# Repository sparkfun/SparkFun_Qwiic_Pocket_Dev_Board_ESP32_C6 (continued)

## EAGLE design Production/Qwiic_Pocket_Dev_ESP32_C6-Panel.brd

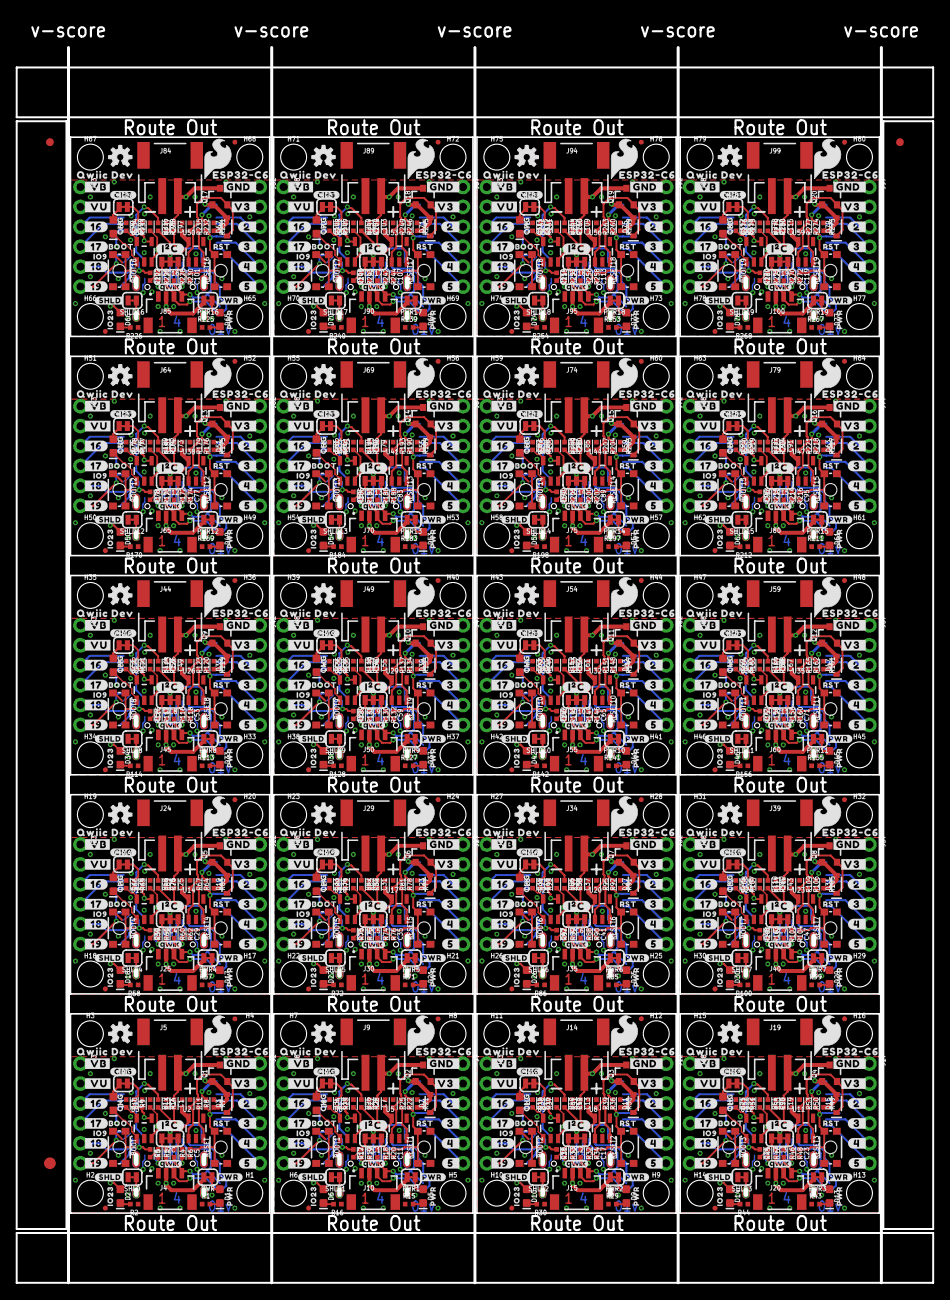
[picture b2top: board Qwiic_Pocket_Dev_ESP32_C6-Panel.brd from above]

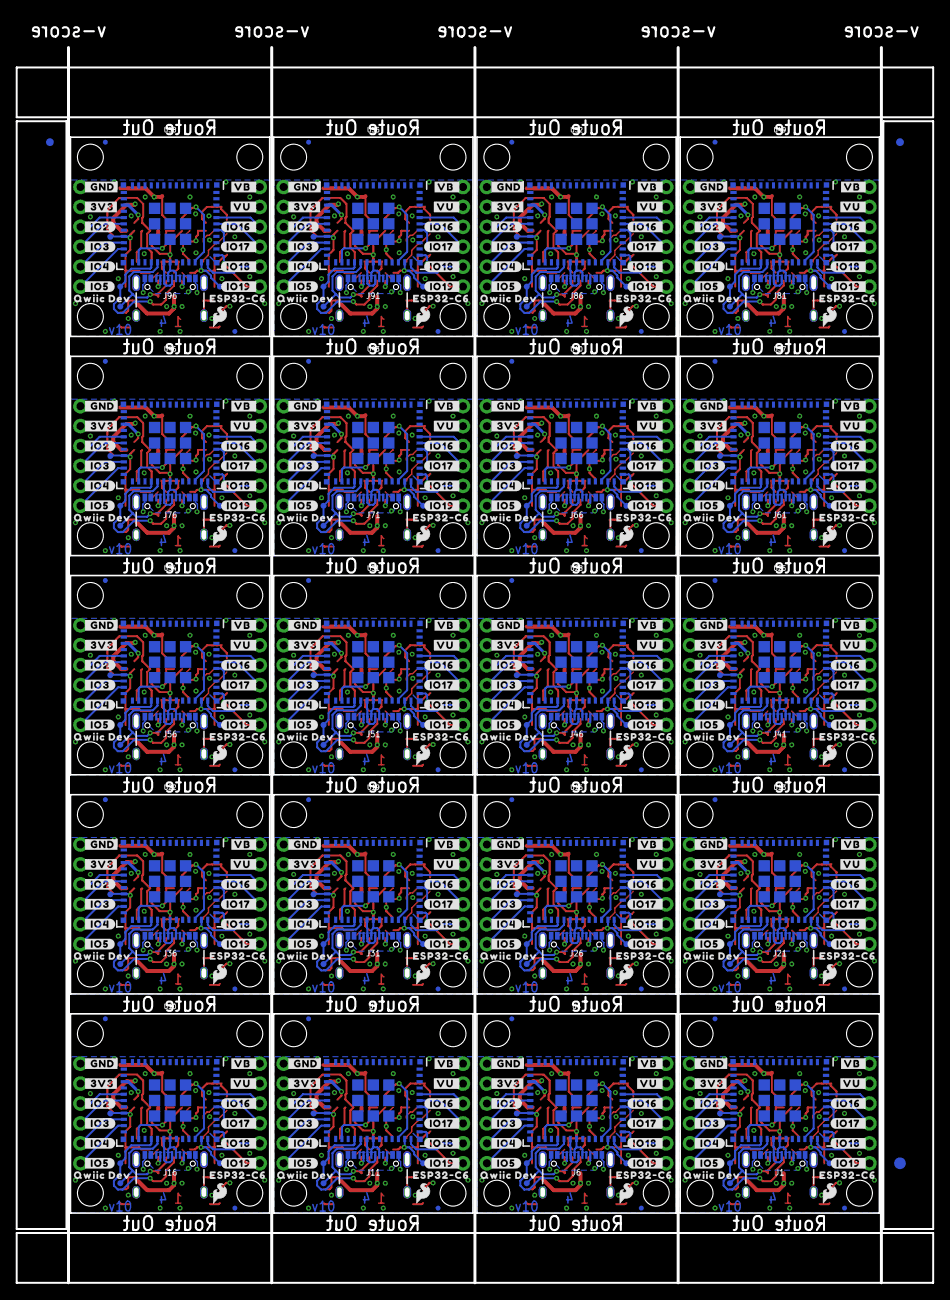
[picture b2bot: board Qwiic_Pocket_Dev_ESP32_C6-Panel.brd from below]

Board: 4 copper layers, 116.8 x 157.5 mm, 1906 parts (463 on the bottom side), 700 nets.

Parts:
BOOT, BOOT1, BOOT2, BOOT3, BOOT4, BOOT5, BOOT6, BOOT7, BOOT8, BOOT9, BOOT10, BOOT11, BOOT12, BOOT13, BOOT14, BOOT15, BOOT16, BOOT17, BOOT18, BOOT19: MOMENTARY-SWITCH-SPST-SMD-4.6X2.8MM; TACTILE_SWITCH_SMD_4.6X2.8MM
C1, C2, C3, C4, C7, C8, C9, C10, C13, C14, C15, C16, C19, C20, C21, C22, C25, C26, C27, C28, C31, C32, C33, C34, C37, C38, C39, C40, C43, C44, C45, C46, C49, C50, C51, C52, C55, C56, C57, C58, C61, C62, C63, C64, C67, C68, C69, C70, C73, C74, C75, C76, C79, C80, C81, C82, C85, C86, C87, C88, C91, C92, C93, C94, C97, C98, C99, C100, C103, C104, C105, C106, C109, C110, C111, C112, C115, C116, C117, C118: 2.2uF; 0402-TIGHT
C5, C11, C17, C23, C29, C35, C41, C47, C53, C59, C65, C71, C77, C83, C89, C95, C101, C107, C113, C119: 0.1uF; 0402-TIGHT
C6, C12, C18, C24, C30, C36, C42, C48, C54, C60, C66, C72, C78, C84, C90, C96, C102, C108, C114, C120: DNP; 0402-TIGHT
CHG, CHG1, CHG2, CHG3, CHG4, CHG5, CHG6, CHG7, CHG8, CHG9, CHG10, CHG11, CHG12, CHG13, CHG14, CHG15, CHG16, CHG17, CHG18, CHG19: JUMPER-SMT_2_NC_TRACE_SILK; SMT-JUMPER_2_NC_TRACE_SILK
D1, D5, D9, D13, D17, D21, D25, D29, D33, D37, D41, D45, D49, D53, D57, D61, D65, D69, D73, D77: LED-0603
D2, D6, D10, D14, D18, D22, D26, D30, D34, D38, D42, D46, D50, D54, D58, D62, D66, D70, D74, D78: BLUE; LED-0603
D3, D7, D11, D15, D19, D23, D27, D31, D35, D39, D43, D47, D51, D55, D59, D63, D67, D71, D75, D79: 1A/23V/620mV; SOD-323
D4, D8, D12, D16, D20, D24, D28, D32, D36, D40, D44, D48, D52, D56, D60, D64, D68, D72, D76, D80: Yellow; LED-0603
E$1, E$2, E$3, E$4: FIDUCIAL-1X2
E$5, E$6: FIDUCIAL-1.5X3
FD1, FD2, FD3, FD4, FD5, FD6, FD7, FD8, FD9, FD10, FD11, FD12, FD13, FD14, FD15, FD16, FD17, FD18, FD19, FD20, FD21, FD22, FD23, FD24, FD25, FD26, FD27, FD28, FD29, FD30, FD31, FD32, FD33, FD34, FD35, FD36, FD37, FD38, FD39, FD40, FD41, FD42, FD43, FD44, FD45, FD46, FD47, FD48, FD49, FD50, FD51, FD52, FD53, FD54, FD55, FD56, FD57, FD58, FD59, FD60, FD61, FD62, FD63, FD64, FD65, FD66, FD67, FD68, FD69, FD70, FD71, FD72, FD73, FD74, FD75, FD76, FD77, FD78, FD79, FD80: FIDUCIALUFIDUCIAL; FIDUCIAL-MICRO
FRAME1, FRAME2, FRAME3, FRAME4, FRAME5, FRAME6, FRAME7, FRAME8, FRAME9, FRAME10, FRAME11, FRAME12, FRAME13, FRAME14, FRAME15, FRAME16, FRAME17, FRAME18, FRAME19, FRAME20: FRAME-LETTER; CREATIVE_COMMONS
H1, H2, H3, H4, H5, H6, H7, H8, H9, H10, H11, H12, H13, H14, H15, H16, H17, H18, H19, H20, H21, H22, H23, H24, H25, H26, H27, H28, H29, H30, H31, H32, H33, H34, H35, H36, H37, H38, H39, H40, H41, H42, H43, H44, H45, H46, H47, H48, H49, H50, H51, H52, H53, H54, H55, H56, H57, H58, H59, H60, H61, H62, H63, H64, H65, H66, H67, H68, H69, H70, H71, H72, H73, H74, H75, H76, H77, H78, H79, H80: STAND-OFF
I2C, I2C1, I2C2, I2C3, I2C4, I2C5, I2C6, I2C7, I2C8, I2C9, I2C10, I2C11, I2C12, I2C13, I2C14, I2C15, I2C16, I2C17, I2C18, I2C19: JUMPER-SMT_3_2-NC_TRACE_SILK; SMT-JUMPER_3_2-NC_TRACE_SILK
J1, J6, J11, J16, J21, J26, J31, J36, J41, J46, J51, J56, J61, J66, J71, J76, J81, J86, J91, J96: USB Female Type C Connector; USB-C-16P_4LAYER-PADS
J2, J3, J7, J8, J12, J13, J17, J18, J22, J23, J27, J28, J32, J33, J37, J38, J42, J43, J47, J48, J52, J53, J57, J58, J62, J63, J67, J68, J72, J73, J77, J78, J82, J83, J87, J88, J92, J93, J97, J98: 1X06_NO_SILK
J4, J10, J15, J20, J25, J30, J35, J40, J45, J50, J55, J60, J65, J70, J75, J80, J85, J90, J95, J100: QWIIC_RIGHT_ANGLE; JST04_1MM_RA
J5, J9, J14, J19, J24, J29, J34, J39, J44, J49, J54, J59, J64, J69, J74, J79, J84, J89, J94, J99: JST-2-SMD
LOGO1, LOGO4, LOGO7, LOGO10, LOGO13, LOGO16, LOGO19, LOGO22, LOGO25, LOGO28, LOGO31, LOGO34, LOGO37, LOGO40, LOGO43, LOGO46, LOGO49, LOGO52, LOGO55, LOGO58: SFE_LOGO_NAME_FLAMEBLANK; BLANK
LOGO2, LOGO5, LOGO8, LOGO11, LOGO14, LOGO17, LOGO20, LOGO23, LOGO26, LOGO29, LOGO32, LOGO35, LOGO38, LOGO41, LOGO44, LOGO47, LOGO50, LOGO53, LOGO56, LOGO59: OSHW-LOGOS; OSHW-LOGO-S
LOGO3, LOGO6, LOGO9, LOGO12, LOGO15, LOGO18, LOGO21, LOGO24, LOGO27, LOGO30, LOGO33, LOGO36, LOGO39, LOGO42, LOGO45, LOGO48, LOGO51, LOGO54, LOGO57, LOGO60: QWIIC_LOGO_3MM; QWIIC_3MM
PWR, PWR1, PWR2, PWR3, PWR4, PWR5, PWR6, PWR7, PWR8, PWR9, PWR10, PWR11, PWR12, PWR13, PWR14, PWR15, PWR16, PWR17, PWR18, PWR19: JUMPER-SMT_2_NC_TRACE_SILK; SMT-JUMPER_2_NC_TRACE_SILK
Q1, Q2, Q3, Q4, Q5, Q6, Q7, Q8, Q9, Q10, Q11, Q12, Q13, Q14, Q15, Q16, Q17, Q18, Q19, Q20: 20V/4.2A/52mΩ/1.4W; SOT23-3
R1, R9, R10, R15, R23, R24, R29, R37, R38, R43, R51, R52, R57, R65, R66, R71, R79, R80, R85, R93, R94, R99, R107, R108, R113, R121, R122, R127, R135, R136, R141, R149, R150, R155, R163, R164, R169, R177, R178, R183, R191, R192, R197, R205, R206, R211, R219, R220, R225, R233, R234, R239, R247, R248, R253, R261, R262, R267, R275, R276: 4.7k; 0402-TIGHT
R2, R3, R4, R16, R17, R18, R30, R31, R32, R44, R45, R46, R58, R59, R60, R72, R73, R74, R86, R87, R88, R100, R101, R102, R114, R115, R116, R128, R129, R130, R142, R143, R144, R156, R157, R158, R170, R171, R172, R184, R185, R186, R198, R199, R200, R212, R213, R214, R226, R227, R228, R240, R241, R242, R254, R255, R256, R268, R269, R270: 2.2k; 0402-TIGHT
R5, R6, R19, R20, R33, R34, R47, R48, R61, R62, R75, R76, R89, R90, R103, R104, R117, R118, R131, R132, R145, R146, R159, R160, R173, R174, R187, R188, R201, R202, R215, R216, R229, R230, R243, R244, R257, R258, R271, R272: 5.1k; 0402-TIGHT
R7, R8, R11, R12, R21, R22, R25, R26, R35, R36, R39, R40, R49, R50, R53, R54, R63, R64, R67, R68, R77, R78, R81, R82, R91, R92, R95, R96, R105, R106, R109, R110, R119, R120, R123, R124, R133, R134, R137, R138, R147, R148, R151, R152, R161, R162, R165, R166, R175, R176, R179, R180, R189, R190, R193, R194, R203, R204, R207, R208, R217, R218, R221, R222, R231, R232, R235, R236, R245, R246, R249, R250, R259, R260, R263, R264, R273, R274, R277, R278: 100k; 0402-TIGHT
R13, R14, R27, R28, R41, R42, R55, R56, R69, R70, R83, R84, R97, R98, R111, R112, R125, R126, R139, R140, R153, R154, R167, R168, R181, R182, R195, R196, R209, R210, R223, R224, R237, R238, R251, R252, R265, R266, R279, R280: 1M; 0402-TIGHT
RESET, RESET1, RESET2, RESET3, RESET4, RESET5, RESET6, RESET7, RESET8, RESET9, RESET10, RESET11, RESET12, RESET13, RESET14, RESET15, RESET16, RESET17, RESET18, RESET19: MOMENTARY-SWITCH-SPST-SMD-4.6X2.8MM; TACTILE_SWITCH_SMD_4.6X2.8MM
SHLD, SHLD1, SHLD2, SHLD3, SHLD4, SHLD5, SHLD6, SHLD7, SHLD8, SHLD9, SHLD10, SHLD11, SHLD12, SHLD13, SHLD14, SHLD15, SHLD16, SHLD17, SHLD18, SHLD19: JUMPER-SMT_2_NC_TRACE_SILK; SMT-JUMPER_2_NC_TRACE_SILK
TP1, TP2, TP3, TP4, TP5, TP6, TP7, TP8, TP9, TP10, TP11, TP12, TP13, TP14, TP15, TP16, TP17, TP18, TP19, TP20, TP21, TP22, TP23, TP24, TP25, TP26, TP27, TP28, TP29, TP30, TP31, TP32, TP33, TP34, TP35, TP36, TP37, TP38, TP39, TP40, TP41, TP42, TP43, TP44, TP45, TP46, TP47, TP48, TP49, TP50, TP51, TP52, TP53, TP54, TP55, TP56, TP57, TP58, TP59, TP60, TP61, TP62, TP63, TP64, TP65, TP66, TP67, TP68, TP69, TP70, TP71, TP72, TP73, TP74, TP75, TP76, TP77, TP78, TP79, TP80: TEST-POINT3; PAD.03X.03
U1, U4, U7, U10, U13, U16, U19, U22, U25, U28, U31, U34, U37, U40, U43, U46, U49, U52, U55, U58: ESP32-C6-MINI-1
U2, U5, U8, U11, U14, U17, U20, U23, U26, U29, U32, U35, U38, U41, U44, U47, U50, U53, U56, U59: RT9080-33GJ5; SOT23-5
U3, U6, U9, U12, U15, U18, U21, U24, U27, U30, U33, U36, U39, U42, U45, U48, U51, U54, U57, U60: MCP73831; SOT23-5
U$1, U$4, U$81, U$121, U$161, U$201, U$241, U$281, U$321, U$361, U$401, U$441, U$481, U$521, U$561, U$601, U$641, U$681, U$721, U$761: #_GND#0
U$2, U$24, U$82, U$122, U$162, U$202, U$242, U$282, U$322, U$362, U$402, U$442, U$482, U$522, U$562, U$602, U$642, U$682, U$722, U$762: #_3V3#0
U$3, U$72, U$112, U$152, U$192, U$232, U$272, U$312, U$352, U$392, U$432, U$472, U$512, U$552, U$592, U$632, U$672, U$712, U$752, U$792: #V3_#0
U$5, U$71, U$111, U$151, U$191, U$231, U$271, U$311, U$351, U$391, U$431, U$471, U$511, U$551, U$591, U$631, U$671, U$711, U$751, U$791: #GND_#0
U$6, U$73, U$113, U$153, U$193, U$233, U$273, U$313, U$353, U$393, U$433, U$473, U$513, U$553, U$593, U$633, U$673, U$713, U$753, U$793: SFE_LOGO_FLAME_.2
U$7, U$53, U$93, U$133, U$173, U$213, U$253, U$293, U$333, U$373, U$413, U$453, U$493, U$533, U$573, U$613, U$653, U$693, U$733, U$773: #VU_#0
U$8, U$54, U$94, U$134, U$174, U$214, U$254, U$294, U$334, U$374, U$414, U$454, U$494, U$534, U$574, U$614, U$654, U$694, U$734, U$774: #_VB#0
U$9, U$25, U$78, U$79, U$118, U$119, U$158, U$159, U$198, U$199, U$238, U$239, U$278, U$279, U$318, U$319, U$358, U$359, U$398, U$399, U$438, U$439, U$478, U$479, U$518, U$519, U$558, U$559, U$598, U$599, U$638, U$639, U$678, U$679, U$718, U$719, U$758, U$759, U$798, U$799: QWIIC_DEV0
U$10, U$74, U$114, U$154, U$194, U$234, U$274, U$314, U$354, U$394, U$434, U$474, U$514, U$554, U$594, U$634, U$674, U$714, U$754, U$794: SFE_LOGO_FLAME_.1
U$11, U$12, U$75, U$76, U$115, U$116, U$155, U$156, U$195, U$196, U$235, U$236, U$275, U$276, U$315, U$316, U$355, U$356, U$395, U$396, U$435, U$436, U$475, U$476, U$515, U$516, U$555, U$556, U$595, U$596, U$635, U$636, U$675, U$676, U$715, U$716, U$755, U$756, U$795, U$796: ESP32#C633
U$13, U$55, U$95, U$135, U$175, U$215, U$255, U$295, U$335, U$375, U$415, U$455, U$495, U$535, U$575, U$615, U$655, U$695, U$735, U$775: #_IO5#0
U$14, U$56, U$96, U$136, U$176, U$216, U$256, U$296, U$336, U$376, U$416, U$456, U$496, U$536, U$576, U$616, U$656, U$696, U$736, U$776: #_IO4#0
U$15, U$57, U$97, U$137, U$177, U$217, U$257, U$297, U$337, U$377, U$417, U$457, U$497, U$537, U$577, U$617, U$657, U$697, U$737, U$777: #_IO3#0
U$16, U$58, U$98, U$138, U$178, U$218, U$258, U$298, U$338, U$378, U$418, U$458, U$498, U$538, U$578, U$618, U$658, U$698, U$738, U$778: #_IO2#0
U$17, U$59, U$99, U$139, U$179, U$219, U$259, U$299, U$339, U$379, U$419, U$459, U$499, U$539, U$579, U$619, U$659, U$699, U$739, U$779: #IO16_#0
U$18, U$60, U$100, U$140, U$180, U$220, U$260, U$300, U$340, U$380, U$420, U$460, U$500, U$540, U$580, U$620, U$660, U$700, U$740, U$780: #IO17_#0
U$19, U$61, U$101, U$141, U$181, U$221, U$261, U$301, U$341, U$381, U$421, U$461, U$501, U$541, U$581, U$621, U$661, U$701, U$741, U$781: #IO18_#0
U$20, U$62, U$102, U$142, U$182, U$222, U$262, U$302, U$342, U$382, U$422, U$462, U$502, U$542, U$582, U$622, U$662, U$702, U$742, U$782: #IO19_#0
U$21, U$63, U$103, U$143, U$183, U$223, U$263, U$303, U$343, U$383, U$423, U$463, U$503, U$543, U$583, U$623, U$663, U$703, U$743, U$783: #5_#0
U$22, U$64, U$104, U$144, U$184, U$224, U$264, U$304, U$344, U$384, U$424, U$464, U$504, U$544, U$584, U$624, U$664, U$704, U$744, U$784: #4_#0
U$23, U$77, U$117, U$157, U$197, U$237, U$277, U$317, U$357, U$397, U$437, U$477, U$517, U$557, U$597, U$637, U$677, U$717, U$757, U$797: #I�C#0
U$26, U$29, U$83, U$123, U$163, U$203, U$243, U$283, U$323, U$363, U$403, U$443, U$483, U$523, U$563, U$603, U$643, U$683, U$723, U$763: #PWR#0
U$27, U$44, U$84, U$124, U$164, U$204, U$244, U$284, U$324, U$364, U$404, U$444, U$484, U$524, U$564, U$604, U$644, U$684, U$724, U$764: #SHLD#0
U$28, U$80, U$120, U$160, U$200, U$240, U$280, U$320, U$360, U$400, U$440, U$480, U$520, U$560, U$600, U$640, U$680, U$720, U$760, U$800: IO230
U$30, U$45, U$85, U$125, U$165, U$205, U$245, U$285, U$325, U$365, U$405, U$445, U$485, U$525, U$565, U$605, U$645, U$685, U$725, U$765: PWR0
U$31, U$46, U$86, U$126, U$166, U$206, U$246, U$286, U$326, U$366, U$406, U$446, U$486, U$526, U$566, U$606, U$646, U$686, U$726, U$766: #CHG#0
U$32, U$49, U$89, U$129, U$169, U$209, U$249, U$289, U$329, U$369, U$409, U$449, U$489, U$529, U$569, U$609, U$649, U$689, U$729, U$769: CHG0
U$33, U$47, U$87, U$127, U$167, U$207, U$247, U$287, U$327, U$367, U$407, U$447, U$487, U$527, U$567, U$607, U$647, U$687, U$727, U$767: BOOT0
U$34, U$48, U$88, U$128, U$168, U$208, U$248, U$288, U$328, U$368, U$408, U$448, U$488, U$528, U$568, U$608, U$648, U$688, U$728, U$768: RST0
U$35, U$50, U$90, U$130, U$170, U$210, U$250, U$290, U$330, U$370, U$410, U$450, U$490, U$530, U$570, U$610, U$650, U$690, U$730, U$770: IO90
U$36, U$51, U$91, U$131, U$171, U$211, U$251, U$291, U$331, U$371, U$411, U$451, U$491, U$531, U$571, U$611, U$651, U$691, U$731, U$771: #VB_#0
U$37, U$52, U$92, U$132, U$172, U$212, U$252, U$292, U$332, U$372, U$412, U$452, U$492, U$532, U$572, U$612, U$652, U$692, U$732, U$772: #_VU#0
U$38, U$65, U$105, U$145, U$185, U$225, U$265, U$305, U$345, U$385, U$425, U$465, U$505, U$545, U$585, U$625, U$665, U$705, U$745, U$785: #3_#0
U$39, U$66, U$106, U$146, U$186, U$226, U$266, U$306, U$346, U$386, U$426, U$466, U$506, U$546, U$586, U$626, U$666, U$706, U$746, U$786: #2_#0
U$40, U$67, U$107, U$147, U$187, U$227, U$267, U$307, U$347, U$387, U$427, U$467, U$507, U$547, U$587, U$627, U$667, U$707, U$747, U$787: #_16#0
U$41, U$68, U$108, U$148, U$188, U$228, U$268, U$308, U$348, U$388, U$428, U$468, U$508, U$548, U$588, U$628, U$668, U$708, U$748, U$788: #_17#0
U$42, U$69, U$109, U$149, U$189, U$229, U$269, U$309, U$349, U$389, U$429, U$469, U$509, U$549, U$589, U$629, U$669, U$709, U$749, U$789: #_18#0
U$43, U$70, U$110, U$150, U$190, U$230, U$270, U$310, U$350, U$390, U$430, U$470, U$510, U$550, U$590, U$630, U$670, U$710, U$750, U$790: #_19#0

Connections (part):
3.3V: C2.1, I2C.2, J2.2, J4.2, PWR.2, R11.2, R12.2, U1.3, U2.5
3.3V1: C8.1, I2C1.2, J7.2, J10.2, PWR1.2, R25.2, R26.2, U4.3, U5.5
3.3V2: C14.1, I2C2.2, J12.2, J15.2, PWR2.2, R39.2, R40.2, U7.3, U8.5
3.3V3: C20.1, I2C3.2, J17.2, J20.2, PWR3.2, R53.2, R54.2, U10.3, U11.5
3.3V4: C26.1, I2C4.2, J22.2, J25.2, PWR4.2, R67.2, R68.2, U13.3, U14.5
3.3V5: C32.1, I2C5.2, J27.2, J30.2, PWR5.2, R81.2, R82.2, U16.3, U17.5
3.3V6: C38.1, I2C6.2, J32.2, J35.2, PWR6.2, R95.2, R96.2, U19.3, U20.5
3.3V7: C44.1, I2C7.2, J37.2, J40.2, PWR7.2, R109.2, R110.2, U22.3, U23.5
3.3V8: C50.1, I2C8.2, J42.2, J45.2, PWR8.2, R123.2, R124.2, U25.3, U26.5
3.3V9: C56.1, I2C9.2, J47.2, J50.2, PWR9.2, R137.2, R138.2, U28.3, U29.5
3.3V10: C62.1, I2C10.2, J52.2, J55.2, PWR10.2, R151.2, R152.2, U31.3, U32.5
3.3V11: C68.1, I2C11.2, J57.2, J60.2, PWR11.2, R165.2, R166.2, U34.3, U35.5
3.3V12: C74.1, I2C12.2, J62.2, J65.2, PWR12.2, R179.2, R180.2, U37.3, U38.5
3.3V13: C80.1, I2C13.2, J67.2, J70.2, PWR13.2, R193.2, R194.2, U40.3, U41.5
3.3V14: C86.1, I2C14.2, J72.2, J75.2, PWR14.2, R207.2, R208.2, U43.3, U44.5
3.3V15: C92.1, I2C15.2, J77.2, J80.2, PWR15.2, R221.2, R222.2, U46.3, U47.5
3.3V16: C98.1, I2C16.2, J82.2, J85.2, PWR16.2, R235.2, R236.2, U49.3, U50.5
3.3V17: C104.1, I2C17.2, J87.2, J90.2, PWR17.2, R249.2, R250.2, U52.3, U53.5
3.3V18: C110.1, I2C18.2, J92.2, J95.2, PWR18.2, R263.2, R264.2, U55.3, U56.5
3.3V19: C116.1, I2C19.2, J97.2, J100.2, PWR19.2, R277.2, R278.2, U58.3, U59.5
EN: C5.1, R11.1, RESET.3, RESET.4, TP4.1, U1.8
EN1: C11.1, R25.1, RESET1.3, RESET1.4, TP8.1, U4.8
EN2: C17.1, R39.1, RESET2.3, RESET2.4, TP12.1, U7.8
EN3: C23.1, R53.1, RESET3.3, RESET3.4, TP16.1, U10.8
EN4: C29.1, R67.1, RESET4.3, RESET4.4, TP20.1, U13.8
EN5: C35.1, R81.1, RESET5.3, RESET5.4, TP24.1, U16.8
EN6: C41.1, R95.1, RESET6.3, RESET6.4, TP28.1, U19.8
EN7: C47.1, R109.1, RESET7.3, RESET7.4, TP32.1, U22.8
EN8: C53.1, R123.1, RESET8.3, RESET8.4, TP36.1, U25.8
EN9: C59.1, R137.1, RESET9.3, RESET9.4, TP40.1, U28.8
EN10: C65.1, R151.1, RESET10.3, RESET10.4, TP44.1, U31.8
EN11: C71.1, R165.1, RESET11.3, RESET11.4, TP48.1, U34.8
EN12: C77.1, R179.1, RESET12.3, RESET12.4, TP52.1, U37.8
EN13: C83.1, R193.1, RESET13.3, RESET13.4, TP56.1, U40.8
EN14: C89.1, R207.1, RESET14.3, RESET14.4, TP60.1, U43.8
EN15: C95.1, R221.1, RESET15.3, RESET15.4, TP64.1, U46.8
EN16: C101.1, R235.1, RESET16.3, RESET16.4, TP68.1, U49.8
EN17: C107.1, R249.1, RESET17.3, RESET17.4, TP72.1, U52.8
EN18: C113.1, R263.1, RESET18.3, RESET18.4, TP76.1, U55.8
EN19: C119.1, R277.1, RESET19.3, RESET19.4, TP80.1, U58.8
GND: BOOT.1, BOOT.2, C1.2, C2.2, C3.2, C4.2, C5.2, C6.2, J1.GND, J1.GND2, J2.1, J4.1, J5.1, R1.1, R2.1, R5.1, R6.1, R7.1, R10.1, R14.1, RESET.1, RESET.2, SHLD.2, U1.1, U1.2, U1.11, U1.14, U1.36, U1.37, U1.38, U1.39, U1.40, U1.41, U1.42, U1.43, U1.44, U1.45, U1.46, U1.47, U1.48, U1.49.1, U1.49.2, U1.49.3, U1.49.4, U1.49.5, U1.49.6, U1.49.7, U1.49.8, U1.49.9, U1.50, U1.51, U1.52, U1.53, U2.2, U3.2
GND1: BOOT1.1, BOOT1.2, C7.2, C8.2, C9.2, C10.2, C11.2, C12.2, J6.GND, J6.GND2, J7.1, J9.1, J10.1, R15.1, R16.1, R19.1, R20.1, R21.1, R24.1, R28.1, RESET1.1, RESET1.2, SHLD1.2, U4.1, U4.2, U4.11, U4.14, U4.36, U4.37, U4.38, U4.39, U4.40, U4.41, U4.42, U4.43, U4.44, U4.45, U4.46, U4.47, U4.48, U4.49.1, U4.49.2, U4.49.3, U4.49.4, U4.49.5, U4.49.6, U4.49.7, U4.49.8, U4.49.9, U4.50, U4.51, U4.52, U4.53, U5.2, U6.2
GND2: BOOT2.1, BOOT2.2, C13.2, C14.2, C15.2, C16.2, C17.2, C18.2, J11.GND, J11.GND2, J12.1, J14.1, J15.1, R29.1, R30.1, R33.1, R34.1, R35.1, R38.1, R42.1, RESET2.1, RESET2.2, SHLD2.2, U7.1, U7.2, U7.11, U7.14, U7.36, U7.37, U7.38, U7.39, U7.40, U7.41, U7.42, U7.43, U7.44, U7.45, U7.46, U7.47, U7.48, U7.49.1, U7.49.2, U7.49.3, U7.49.4, U7.49.5, U7.49.6, U7.49.7, U7.49.8, U7.49.9, U7.50, U7.51, U7.52, U7.53, U8.2, U9.2
GND3: BOOT3.1, BOOT3.2, C19.2, C20.2, C21.2, C22.2, C23.2, C24.2, J16.GND, J16.GND2, J17.1, J19.1, J20.1, R43.1, R44.1, R47.1, R48.1, R49.1, R52.1, R56.1, RESET3.1, RESET3.2, SHLD3.2, U10.1, U10.2, U10.11, U10.14, U10.36, U10.37, U10.38, U10.39, U10.40, U10.41, U10.42, U10.43, U10.44, U10.45, U10.46, U10.47, U10.48, U10.49.1, U10.49.2, U10.49.3, U10.49.4, U10.49.5, U10.49.6, U10.49.7, U10.49.8, U10.49.9, U10.50, U10.51, U10.52, U10.53, U11.2, U12.2
GND4: BOOT4.1, BOOT4.2, C25.2, C26.2, C27.2, C28.2, C29.2, C30.2, J21.GND, J21.GND2, J22.1, J24.1, J25.1, R57.1, R58.1, R61.1, R62.1, R63.1, R66.1, R70.1, RESET4.1, RESET4.2, SHLD4.2, U13.1, U13.2, U13.11, U13.14, U13.36, U13.37, U13.38, U13.39, U13.40, U13.41, U13.42, U13.43, U13.44, U13.45, U13.46, U13.47, U13.48, U13.49.1, U13.49.2, U13.49.3, U13.49.4, U13.49.5, U13.49.6, U13.49.7, U13.49.8, U13.49.9, U13.50, U13.51, U13.52, U13.53, U14.2, U15.2
GND5: BOOT5.1, BOOT5.2, C31.2, C32.2, C33.2, C34.2, C35.2, C36.2, J26.GND, J26.GND2, J27.1, J29.1, J30.1, R71.1, R72.1, R75.1, R76.1, R77.1, R80.1, R84.1, RESET5.1, RESET5.2, SHLD5.2, U16.1, U16.2, U16.11, U16.14, U16.36, U16.37, U16.38, U16.39, U16.40, U16.41, U16.42, U16.43, U16.44, U16.45, U16.46, U16.47, U16.48, U16.49.1, U16.49.2, U16.49.3, U16.49.4, U16.49.5, U16.49.6, U16.49.7, U16.49.8, U16.49.9, U16.50, U16.51, U16.52, U16.53, U17.2, U18.2
GND6: BOOT6.1, BOOT6.2, C37.2, C38.2, C39.2, C40.2, C41.2, C42.2, J31.GND, J31.GND2, J32.1, J34.1, J35.1, R85.1, R86.1, R89.1, R90.1, R91.1, R94.1, R98.1, RESET6.1, RESET6.2, SHLD6.2, U19.1, U19.2, U19.11, U19.14, U19.36, U19.37, U19.38, U19.39, U19.40, U19.41, U19.42, U19.43, U19.44, U19.45, U19.46, U19.47, U19.48, U19.49.1, U19.49.2, U19.49.3, U19.49.4, U19.49.5, U19.49.6, U19.49.7, U19.49.8, U19.49.9, U19.50, U19.51, U19.52, U19.53, U20.2, U21.2
GND7: BOOT7.1, BOOT7.2, C43.2, C44.2, C45.2, C46.2, C47.2, C48.2, J36.GND, J36.GND2, J37.1, J39.1, J40.1, R99.1, R100.1, R103.1, R104.1, R105.1, R108.1, R112.1, RESET7.1, RESET7.2, SHLD7.2, U22.1, U22.2, U22.11, U22.14, U22.36, U22.37, U22.38, U22.39, U22.40, U22.41, U22.42, U22.43, U22.44, U22.45, U22.46, U22.47, U22.48, U22.49.1, U22.49.2, U22.49.3, U22.49.4, U22.49.5, U22.49.6, U22.49.7, U22.49.8, U22.49.9, U22.50, U22.51, U22.52, U22.53, U23.2, U24.2
GND8: BOOT8.1, BOOT8.2, C49.2, C50.2, C51.2, C52.2, C53.2, C54.2, J41.GND, J41.GND2, J42.1, J44.1, J45.1, R113.1, R114.1, R117.1, R118.1, R119.1, R122.1, R126.1, RESET8.1, RESET8.2, SHLD8.2, U25.1, U25.2, U25.11, U25.14, U25.36, U25.37, U25.38, U25.39, U25.40, U25.41, U25.42, U25.43, U25.44, U25.45, U25.46, U25.47, U25.48, U25.49.1, U25.49.2, U25.49.3, U25.49.4, U25.49.5, U25.49.6, U25.49.7, U25.49.8, U25.49.9, U25.50, U25.51, U25.52, U25.53, U26.2, U27.2
GND9: BOOT9.1, BOOT9.2, C55.2, C56.2, C57.2, C58.2, C59.2, C60.2, J46.GND, J46.GND2, J47.1, J49.1, J50.1, R127.1, R128.1, R131.1, R132.1, R133.1, R136.1, R140.1, RESET9.1, RESET9.2, SHLD9.2, U28.1, U28.2, U28.11, U28.14, U28.36, U28.37, U28.38, U28.39, U28.40, U28.41, U28.42, U28.43, U28.44, U28.45, U28.46, U28.47, U28.48, U28.49.1, U28.49.2, U28.49.3, U28.49.4, U28.49.5, U28.49.6, U28.49.7, U28.49.8, U28.49.9, U28.50, U28.51, U28.52, U28.53, U29.2, U30.2
GND10: BOOT10.1, BOOT10.2, C61.2, C62.2, C63.2, C64.2, C65.2, C66.2, J51.GND, J51.GND2, J52.1, J54.1, J55.1, R141.1, R142.1, R145.1, R146.1, R147.1, R150.1, R154.1, RESET10.1, RESET10.2, SHLD10.2, U31.1, U31.2, U31.11, U31.14, U31.36, U31.37, U31.38, U31.39, U31.40, U31.41, U31.42, U31.43, U31.44, U31.45, U31.46, U31.47, U31.48, U31.49.1, U31.49.2, U31.49.3, U31.49.4, U31.49.5, U31.49.6, U31.49.7, U31.49.8, U31.49.9, U31.50, U31.51, U31.52, U31.53, U32.2, U33.2
GND11: BOOT11.1, BOOT11.2, C67.2, C68.2, C69.2, C70.2, C71.2, C72.2, J56.GND, J56.GND2, J57.1, J59.1, J60.1, R155.1, R156.1, R159.1, R160.1, R161.1, R164.1, R168.1, RESET11.1, RESET11.2, SHLD11.2, U34.1, U34.2, U34.11, U34.14, U34.36, U34.37, U34.38, U34.39, U34.40, U34.41, U34.42, U34.43, U34.44, U34.45, U34.46, U34.47, U34.48, U34.49.1, U34.49.2, U34.49.3, U34.49.4, U34.49.5, U34.49.6, U34.49.7, U34.49.8, U34.49.9, U34.50, U34.51, U34.52, U34.53, U35.2, U36.2
GND12: BOOT12.1, BOOT12.2, C73.2, C74.2, C75.2, C76.2, C77.2, C78.2, J61.GND, J61.GND2, J62.1, J64.1, J65.1, R169.1, R170.1, R173.1, R174.1, R175.1, R178.1, R182.1, RESET12.1, RESET12.2, SHLD12.2, U37.1, U37.2, U37.11, U37.14, U37.36, U37.37, U37.38, U37.39, U37.40, U37.41, U37.42, U37.43, U37.44, U37.45, U37.46, U37.47, U37.48, U37.49.1, U37.49.2, U37.49.3, U37.49.4, U37.49.5, U37.49.6, U37.49.7, U37.49.8, U37.49.9, U37.50, U37.51, U37.52, U37.53, U38.2, U39.2
GND13: BOOT13.1, BOOT13.2, C79.2, C80.2, C81.2, C82.2, C83.2, C84.2, J66.GND, J66.GND2, J67.1, J69.1, J70.1, R183.1, R184.1, R187.1, R188.1, R189.1, R192.1, R196.1, RESET13.1, RESET13.2, SHLD13.2, U40.1, U40.2, U40.11, U40.14, U40.36, U40.37, U40.38, U40.39, U40.40, U40.41, U40.42, U40.43, U40.44, U40.45, U40.46, U40.47, U40.48, U40.49.1, U40.49.2, U40.49.3, U40.49.4, U40.49.5, U40.49.6, U40.49.7, U40.49.8, U40.49.9, U40.50, U40.51, U40.52, U40.53, U41.2, U42.2
GND14: BOOT14.1, BOOT14.2, C85.2, C86.2, C87.2, C88.2, C89.2, C90.2, J71.GND, J71.GND2, J72.1, J74.1, J75.1, R197.1, R198.1, R201.1, R202.1, R203.1, R206.1, R210.1, RESET14.1, RESET14.2, SHLD14.2, U43.1, U43.2, U43.11, U43.14, U43.36, U43.37, U43.38, U43.39, U43.40, U43.41, U43.42, U43.43, U43.44, U43.45, U43.46, U43.47, U43.48, U43.49.1, U43.49.2, U43.49.3, U43.49.4, U43.49.5, U43.49.6, U43.49.7, U43.49.8, U43.49.9, U43.50, U43.51, U43.52, U43.53, U44.2, U45.2
GND15: BOOT15.1, BOOT15.2, C91.2, C92.2, C93.2, C94.2, C95.2, C96.2, J76.GND, J76.GND2, J77.1, J79.1, J80.1, R211.1, R212.1, R215.1, R216.1, R217.1, R220.1, R224.1, RESET15.1, RESET15.2, SHLD15.2, U46.1, U46.2, U46.11, U46.14, U46.36, U46.37, U46.38, U46.39, U46.40, U46.41, U46.42, U46.43, U46.44, U46.45, U46.46, U46.47, U46.48, U46.49.1, U46.49.2, U46.49.3, U46.49.4, U46.49.5, U46.49.6, U46.49.7, U46.49.8, U46.49.9, U46.50, U46.51, U46.52, U46.53, U47.2, U48.2
GND16: BOOT16.1, BOOT16.2, C97.2, C98.2, C99.2, C100.2, C101.2, C102.2, J81.GND, J81.GND2, J82.1, J84.1, J85.1, R225.1, R226.1, R229.1, R230.1, R231.1, R234.1, R238.1, RESET16.1, RESET16.2, SHLD16.2, U49.1, U49.2, U49.11, U49.14, U49.36, U49.37, U49.38, U49.39, U49.40, U49.41, U49.42, U49.43, U49.44, U49.45, U49.46, U49.47, U49.48, U49.49.1, U49.49.2, U49.49.3, U49.49.4, U49.49.5, U49.49.6, U49.49.7, U49.49.8, U49.49.9, U49.50, U49.51, U49.52, U49.53, U50.2, U51.2
GND17: BOOT17.1, BOOT17.2, C103.2, C104.2, C105.2, C106.2, C107.2, C108.2, J86.GND, J86.GND2, J87.1, J89.1, J90.1, R239.1, R240.1, R243.1, R244.1, R245.1, R248.1, R252.1, RESET17.1, RESET17.2, SHLD17.2, U52.1, U52.2, U52.11, U52.14, U52.36, U52.37, U52.38, U52.39, U52.40, U52.41, U52.42, U52.43, U52.44, U52.45, U52.46, U52.47, U52.48, U52.49.1, U52.49.2, U52.49.3, U52.49.4, U52.49.5, U52.49.6, U52.49.7, U52.49.8, U52.49.9, U52.50, U52.51, U52.52, U52.53, U53.2, U54.2
GND18: BOOT18.1, BOOT18.2, C109.2, C110.2, C111.2, C112.2, C113.2, C114.2, J91.GND, J91.GND2, J92.1, J94.1, J95.1, R253.1, R254.1, R257.1, R258.1, R259.1, R262.1, R266.1, RESET18.1, RESET18.2, SHLD18.2, U55.1, U55.2, U55.11, U55.14, U55.36, U55.37, U55.38, U55.39, U55.40, U55.41, U55.42, U55.43, U55.44, U55.45, U55.46, U55.47, U55.48, U55.49.1, U55.49.2, U55.49.3, U55.49.4, U55.49.5, U55.49.6, U55.49.7, U55.49.8, U55.49.9, U55.50, U55.51, U55.52, U55.53, U56.2, U57.2
GND19: BOOT19.1, BOOT19.2, C115.2, C116.2, C117.2, C118.2, C119.2, C120.2, J96.GND, J96.GND2, J97.1, J99.1, J100.1, R267.1, R268.1, R271.1, R272.1, R273.1, R276.1, R280.1, RESET19.1, RESET19.2, SHLD19.2, U58.1, U58.2, U58.11, U58.14, U58.36, U58.37, U58.38, U58.39, U58.40, U58.41, U58.42, U58.43, U58.44, U58.45, U58.46, U58.47, U58.48, U58.49.1, U58.49.2, U58.49.3, U58.49.4, U58.49.5, U58.49.6, U58.49.7, U58.49.8, U58.49.9, U58.50, U58.51, U58.52, U58.53, U59.2, U60.2
IO1: J7.5, U4.9
IO1/V_BATT_1: R27.1, R28.2, U4.13
IO1/V_BATT_2: R13.1, R14.2, U1.13
IO1/V_BATT_3: R41.1, R42.2, U7.13
IO1/V_BATT_4: R55.1, R56.2, U10.13
IO1/V_BATT_5: R69.1, R70.2, U13.13
IO1/V_BATT_6: R83.1, R84.2, U16.13
IO1/V_BATT_7: R97.1, R98.2, U19.13
IO1/V_BATT_8: R111.1, R112.2, U22.13
IO1/V_BATT_9: R125.1, R126.2, U25.13
IO1/V_BATT_10: R139.1, R140.2, U28.13
IO1/V_BATT_11: R153.1, R154.2, U31.13
IO1/V_BATT_12: R167.1, R168.2, U34.13
IO1/V_BATT_13: R181.1, R182.2, U37.13
IO1/V_BATT_14: R195.1, R196.2, U40.13
IO1/V_BATT_15: R209.1, R210.2, U43.13
IO1/V_BATT_16: R223.1, R224.2, U46.13
IO1/V_BATT_17: R237.1, R238.2, U49.13
IO1/V_BATT_18: R251.1, R252.2, U52.13
IO1/V_BATT_19: R265.1, R266.2, U55.13
IO1/V_BATT_20: R279.1, R280.2, U58.13
IO2: J2.3, U1.5
IO3: J2.4, U1.6
IO4: J2.5, U1.9
IO5: J2.6, U1.10
IO6: J7.6, U4.10
IO6/SDA: J4.3, R3.1, TP2.1, U1.15
IO6/SDA1: J10.3, R17.1, TP6.1, U4.15
IO6/SDA2: J15.3, R31.1, TP10.1, U7.15
IO6/SDA3: J20.3, R45.1, TP14.1, U10.15
IO6/SDA4: J25.3, R59.1, TP18.1, U13.15
IO6/SDA5: J30.3, R73.1, TP22.1, U16.15
IO6/SDA6: J35.3, R87.1, TP26.1, U19.15
IO6/SDA7: J40.3, R101.1, TP30.1, U22.15
IO6/SDA8: J45.3, R115.1, TP34.1, U25.15
IO6/SDA9: J50.3, R129.1, TP38.1, U28.15
IO6/SDA10: J55.3, R143.1, TP42.1, U31.15
IO6/SDA11: J60.3, R157.1, TP46.1, U34.15
IO6/SDA12: J65.3, R171.1, TP50.1, U37.15
IO6/SDA13: J70.3, R185.1, TP54.1, U40.15
IO6/SDA14: J75.3, R199.1, TP58.1, U43.15
IO6/SDA15: J80.3, R213.1, TP62.1, U46.15
IO6/SDA16: J85.3, R227.1, TP66.1, U49.15
IO6/SDA17: J90.3, R241.1, TP70.1, U52.15
IO6/SDA18: J95.3, R255.1, TP74.1, U55.15
IO6/SDA19: J100.3, R269.1, TP78.1, U58.15
IO7: J7.3, U4.5
IO7/SCL: J4.4, R4.2, TP1.1, U1.16
IO7/SCL1: J10.4, R18.2, TP5.1, U4.16
IO7/SCL2: J15.4, R32.2, TP9.1, U7.16
IO7/SCL3: J20.4, R46.2, TP13.1, U10.16
IO7/SCL4: J25.4, R60.2, TP17.1, U13.16
IO7/SCL5: J30.4, R74.2, TP21.1, U16.16
IO7/SCL6: J35.4, R88.2, TP25.1, U19.16
IO7/SCL7: J40.4, R102.2, TP29.1, U22.16
IO7/SCL8: J45.4, R116.2, TP33.1, U25.16
IO7/SCL9: J50.4, R130.2, TP37.1, U28.16
IO7/SCL10: J55.4, R144.2, TP41.1, U31.16
IO7/SCL11: J60.4, R158.2, TP45.1, U34.16
IO7/SCL12: J65.4, R172.2, TP49.1, U37.16
IO7/SCL13: J70.4, R186.2, TP53.1, U40.16
IO7/SCL14: J75.4, R200.2, TP57.1, U43.16
IO7/SCL15: J80.4, R214.2, TP61.1, U46.16
IO7/SCL16: J85.4, R228.2, TP65.1, U49.16
IO7/SCL17: J90.4, R242.2, TP69.1, U52.16
IO7/SCL18: J95.4, R256.2, TP73.1, U55.16
IO7/SCL19: J100.4, R270.2, TP77.1, U58.16
IO8: J7.4, U4.6
IO9: J8.5, U4.24
IO9/BOOT: BOOT.3, BOOT.4, C6.1, TP3.1, U1.23
IO9/BOOT1: BOOT1.3, BOOT1.4, C12.1, TP7.1, U4.23
IO9/BOOT2: BOOT2.3, BOOT2.4, C18.1, TP11.1, U7.23
IO9/BOOT3: BOOT3.3, BOOT3.4, C24.1, TP15.1, U10.23
IO9/BOOT4: BOOT4.3, BOOT4.4, C30.1, TP19.1, U13.23
IO9/BOOT5: BOOT5.3, BOOT5.4, C36.1, TP23.1, U16.23
IO9/BOOT6: BOOT6.3, BOOT6.4, C42.1, TP27.1, U19.23
IO9/BOOT7: BOOT7.3, BOOT7.4, C48.1, TP31.1, U22.23
IO9/BOOT8: BOOT8.3, BOOT8.4, C54.1, TP35.1, U25.23
IO9/BOOT9: BOOT9.3, BOOT9.4, C60.1, TP39.1, U28.23
IO9/BOOT10: BOOT10.3, BOOT10.4, C66.1, TP43.1, U31.23
IO9/BOOT11: BOOT11.3, BOOT11.4, C72.1, TP47.1, U34.23
IO9/BOOT12: BOOT12.3, BOOT12.4, C78.1, TP51.1, U37.23
IO9/BOOT13: BOOT13.3, BOOT13.4, C84.1, TP55.1, U40.23
IO9/BOOT14: BOOT14.3, BOOT14.4, C90.1, TP59.1, U43.23
IO9/BOOT15: BOOT15.3, BOOT15.4, C96.1, TP63.1, U46.23
IO9/BOOT16: BOOT16.3, BOOT16.4, C102.1, TP67.1, U49.23
IO9/BOOT17: BOOT17.3, BOOT17.4, C108.1, TP71.1, U52.23
IO9/BOOT18: BOOT18.3, BOOT18.4, C114.1, TP75.1, U55.23
IO9/BOOT19: BOOT19.3, BOOT19.4, C120.1, TP79.1, U58.23
IO10: J8.6, U4.25
IO11: J12.5, U7.9
IO12: J12.6, U7.10
IO12/USB_N: J1.A7, J1.B7, U1.17
IO12/USB_N1: J6.A7, J6.B7, U4.17
IO12/USB_N2: J11.A7, J11.B7, U7.17
IO12/USB_N3: J16.A7, J16.B7, U10.17
IO12/USB_N4: J21.A7, J21.B7, U13.17
IO12/USB_N5: J26.A7, J26.B7, U16.17
IO12/USB_N6: J31.A7, J31.B7, U19.17
IO12/USB_N7: J36.A7, J36.B7, U22.17
IO12/USB_N8: J41.A7, J41.B7, U25.17
IO12/USB_N9: J46.A7, J46.B7, U28.17
IO12/USB_N10: J51.A7, J51.B7, U31.17
IO12/USB_N11: J56.A7, J56.B7, U34.17
IO12/USB_N12: J61.A7, J61.B7, U37.17
IO12/USB_N13: J66.A7, J66.B7, U40.17
IO12/USB_N14: J71.A7, J71.B7, U43.17
IO12/USB_N15: J76.A7, J76.B7, U46.17
IO12/USB_N16: J81.A7, J81.B7, U49.17
IO12/USB_N17: J86.A7, J86.B7, U52.17
IO12/USB_N18: J91.A7, J91.B7, U55.17
IO12/USB_N19: J96.A7, J96.B7, U58.17
IO13: J12.3, U7.5
IO13/USB_P: J1.A6, J1.B6, U1.18
IO13/USB_P1: J6.A6, J6.B6, U4.18
IO13/USB_P2: J11.A6, J11.B6, U7.18
IO13/USB_P3: J16.A6, J16.B6, U10.18
IO13/USB_P4: J21.A6, J21.B6, U13.18
IO13/USB_P5: J26.A6, J26.B6, U16.18
IO13/USB_P6: J31.A6, J31.B6, U19.18
IO13/USB_P7: J36.A6, J36.B6, U22.18
IO13/USB_P8: J41.A6, J41.B6, U25.18
IO13/USB_P9: J46.A6, J46.B6, U28.18
IO13/USB_P10: J51.A6, J51.B6, U31.18
IO13/USB_P11: J56.A6, J56.B6, U34.18
IO13/USB_P12: J61.A6, J61.B6, U37.18
IO13/USB_P13: J66.A6, J66.B6, U40.18
IO13/USB_P14: J71.A6, J71.B6, U43.18
IO13/USB_P15: J76.A6, J76.B6, U46.18
IO13/USB_P16: J81.A6, J81.B6, U49.18
IO13/USB_P17: J86.A6, J86.B6, U52.18
IO13/USB_P18: J91.A6, J91.B6, U55.18
IO13/USB_P19: J96.A6, J96.B6, U58.18
IO14: J12.4, U7.6
IO15: J13.5, U7.24
IO16: J13.6, U7.25
IO16/TX: J3.3, U1.31
IO16/TX1: J8.3, U4.31
IO16/TX2: J13.3, U7.31
IO16/TX3: J18.3, U10.31
IO16/TX4: J23.3, U13.31
IO16/TX5: J28.3, U16.31
IO16/TX6: J33.3, U19.31
IO16/TX7: J38.3, U22.31
IO16/TX8: J43.3, U25.31
IO16/TX9: J48.3, U28.31
IO16/TX10: J53.3, U31.31
IO16/TX11: J58.3, U34.31
IO16/TX12: J63.3, U37.31
IO16/TX13: J68.3, U40.31
IO16/TX14: J73.3, U43.31
IO16/TX15: J78.3, U46.31
IO16/TX16: J83.3, U49.31
IO16/TX17: J88.3, U52.31
IO16/TX18: J93.3, U55.31
IO16/TX19: J98.3, U58.31
IO17: J17.5, U10.9
IO17/RX: J3.4, U1.30
IO17/RX1: J8.4, U4.30
IO17/RX2: J13.4, U7.30
IO17/RX3: J18.4, U10.30
IO17/RX4: J23.4, U13.30
IO17/RX5: J28.4, U16.30
IO17/RX6: J33.4, U19.30
IO17/RX7: J38.4, U22.30
IO17/RX8: J43.4, U25.30
IO17/RX9: J48.4, U28.30
IO17/RX10: J53.4, U31.30
IO17/RX11: J58.4, U34.30
IO17/RX12: J63.4, U37.30
IO17/RX13: J68.4, U40.30
IO17/RX14: J73.4, U43.30
IO17/RX15: J78.4, U46.30
IO17/RX16: J83.4, U49.30
IO17/RX17: J88.4, U52.30
IO17/RX18: J93.4, U55.30
IO17/RX19: J98.4, U58.30
IO18: J3.5, U1.24
IO19: J3.6, U1.25
IO20: J17.6, U10.10
IO21: J17.3, U10.5
IO22: J17.4, U10.6
IO23: J18.5, U10.24
IO23/STAT: D2.A, U1.29
IO23/STAT1: D6.A, U4.29
IO23/STAT2: D10.A, U7.29
IO23/STAT3: D14.A, U10.29
IO23/STAT4: D18.A, U13.29
IO23/STAT5: D22.A, U16.29
IO23/STAT6: D26.A, U19.29
IO23/STAT7: D30.A, U22.29
IO23/STAT8: D34.A, U25.29
IO23/STAT9: D38.A, U28.29
IO23/STAT10: D42.A, U31.29
IO23/STAT11: D46.A, U34.29
IO23/STAT12: D50.A, U37.29
IO23/STAT13: D54.A, U40.29
IO23/STAT14: D58.A, U43.29
IO23/STAT15: D62.A, U46.29
IO23/STAT16: D66.A, U49.29
IO23/STAT17: D70.A, U52.29
IO23/STAT18: D74.A, U55.29
IO23/STAT19: D78.A, U58.29
IO24: J18.6, U10.25
IO25: J22.5, U13.9
IO26: J22.6, U13.10
IO27: J22.3, U13.5
IO28: J22.4, U13.6
IO29: J23.5, U13.24
IO30: J23.6, U13.25
IO31: J27.5, U16.9
IO32: J27.6, U16.10
IO33: J27.3, U16.5
IO34: J27.4, U16.6
IO35: J28.5, U16.24
IO36: J28.6, U16.25
IO37: J32.5, U19.9
IO38: J32.6, U19.10
IO39: J32.3, U19.5
IO40: J32.4, U19.6
IO41: J33.5, U19.24
IO42: J33.6, U19.25
IO43: J37.5, U22.9
IO44: J37.6, U22.10
IO45: J37.3, U22.5
IO46: J37.4, U22.6
IO47: J38.5, U22.24
IO48: J38.6, U22.25
IO49: J42.5, U25.9
IO50: J42.6, U25.10
IO51: J42.3, U25.5
IO52: J42.4, U25.6
IO53: J43.5, U25.24
IO54: J43.6, U25.25
IO55: J47.5, U28.9
IO56: J47.6, U28.10
IO57: J47.3, U28.5
IO58: J47.4, U28.6
IO59: J48.5, U28.24
IO60: J48.6, U28.25
IO61: J52.5, U31.9
IO62: J52.6, U31.10
IO63: J52.3, U31.5
IO64: J52.4, U31.6
IO65: J53.5, U31.24
IO66: J53.6, U31.25
IO67: J57.5, U34.9
IO68: J57.6, U34.10
IO69: J57.3, U34.5
IO70: J57.4, U34.6
IO71: J58.5, U34.24
IO72: J58.6, U34.25
IO73: J62.5, U37.9
IO74: J62.6, U37.10
IO75: J62.3, U37.5
IO76: J62.4, U37.6
IO77: J63.5, U37.24
IO78: J63.6, U37.25
IO79: J67.5, U40.9
IO80: J67.6, U40.10
IO81: J67.3, U40.5
IO82: J67.4, U40.6
IO83: J68.5, U40.24
IO84: J68.6, U40.25
IO85: J72.5, U43.9
IO86: J72.6, U43.10
IO87: J72.3, U43.5
IO88: J72.4, U43.6
IO89: J73.5, U43.24
IO90: J73.6, U43.25
IO91: J77.5, U46.9
IO92: J77.6, U46.10
IO93: J77.3, U46.5
IO94: J77.4, U46.6
IO95: J78.5, U46.24
IO96: J78.6, U46.25
IO97: J82.5, U49.9
IO98: J82.6, U49.10
IO99: J82.3, U49.5
IO100: J82.4, U49.6
IO101: J83.5, U49.24
IO102: J83.6, U49.25
IO103: J87.5, U52.9
IO104: J87.6, U52.10
IO105: J87.3, U52.5
IO106: J87.4, U52.6
IO107: J88.5, U52.24
IO108: J88.6, U52.25
IO109: J92.5, U55.9
IO110: J92.6, U55.10
IO111: J92.3, U55.5
IO112: J92.4, U55.6
IO113: J93.5, U55.24
IO114: J93.6, U55.25
IO115: J97.5, U58.9
IO116: J97.6, U58.10
IO117: J97.3, U58.5
IO118: J97.4, U58.6
IO119: J98.5, U58.24
IO120: J98.6, U58.25
unnamed: D1.C, R1.2
unnamed: D1.A, PWR.1
unnamed: D2.C, R2.2
unnamed: I2C.3, R3.2
unnamed: I2C.1, R4.1
unnamed: R8.2, U2.3
unnamed: J1.B5, R5.2
unnamed: J1.A5, R6.2
unnamed: C1.1, D3.C, Q1.2, R8.1, U2.1
unnamed: D4.C, U3.1
unnamed: CHG.1, D4.A
unnamed: CHG.2, R9.1
unnamed: R10.2, U3.5
unnamed: R12.1, U1.22
unnamed: I2C1.3, R17.2
unnamed: I2C1.1, R18.1
unnamed: J6.B5, R19.2
unnamed: J6.A5, R20.2
unnamed: R22.2, U5.3
unnamed: C7.1, D7.C, Q2.2, R22.1, U5.1
unnamed: D8.C, U6.1
unnamed: CHG1.1, D8.A
unnamed: CHG1.2, R23.1
unnamed: R24.2, U6.5
unnamed: D5.C, R15.2
unnamed: D5.A, PWR1.1
unnamed: D6.C, R16.2
unnamed: R26.1, U4.22
unnamed: I2C2.3, R31.2
unnamed: I2C2.1, R32.1
unnamed: J11.B5, R33.2
unnamed: J11.A5, R34.2
unnamed: R36.2, U8.3
unnamed: C13.1, D11.C, Q3.2, R36.1, U8.1
unnamed: D12.C, U9.1
unnamed: CHG2.1, D12.A
unnamed: CHG2.2, R37.1
unnamed: R38.2, U9.5
unnamed: D9.C, R29.2
unnamed: D9.A, PWR2.1
unnamed: D10.C, R30.2
unnamed: R40.1, U7.22
unnamed: I2C3.3, R45.2
unnamed: I2C3.1, R46.1
unnamed: J16.B5, R47.2
unnamed: J16.A5, R48.2
unnamed: R50.2, U11.3
unnamed: C19.1, D15.C, Q4.2, R50.1, U11.1
unnamed: D16.C, U12.1
unnamed: CHG3.1, D16.A
unnamed: CHG3.2, R51.1
unnamed: R52.2, U12.5
unnamed: D13.C, R43.2
unnamed: D13.A, PWR3.1
unnamed: D14.C, R44.2
unnamed: R54.1, U10.22
unnamed: I2C4.3, R59.2
unnamed: I2C4.1, R60.1
unnamed: J21.B5, R61.2
unnamed: J21.A5, R62.2
unnamed: R64.2, U14.3
unnamed: C25.1, D19.C, Q5.2, R64.1, U14.1
unnamed: D20.C, U15.1
unnamed: CHG4.1, D20.A
unnamed: CHG4.2, R65.1
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
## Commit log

2023-06-23 Add documents
2023-06-23 Add hardware library file for ESP32-C6-MINI
2023-06-23 Add initial design
2023-06-27 Design review updates
    Add voltage regulator voltage and current maximums
    Add 4-layer stackup info to ordering instructions
    Add info about boot button usage
    Fix blue LED resistor value
    Nudge N$14 to get GND to connect to battery pad
    Add tRestrict between C1 and C2
2023-06-27 Rename Eagle files to match product name
2023-06-27 Move fiducials
    Moved inward to make it easier for PnP to handle single boards
    Decided to flip the fiducial corners, made it easier to move inwards
2023-06-28 Add note about SHLD jumper
2023-06-29 Add battery voltage divider
2023-06-29 Improve ground pour
2023-07-27 Initial docs commit
    Initial documentation commit. Adding GH pages build/config files & first draft of documentation files.
2023-07-31 Change STAT LED to GPIO23
    GPIO20 likes to magically start toggling the LED when touching GPIO19. Something to do with the SDIO pins, I think
2023-07-31 v10 updates
    Bump version number
    Update STAT LED IO silk label
2023-08-01 Design review updates
    Fix acid trap
    Approve DRC errors on jumpers
2023-08-01 Remove proto production files
    Didn't meant to add these before, whoops!
2023-08-01 Add v10 panel files
2023-08-24 Change battery voltage divider resistors to 1M Ohm
2023-09-19 Change C6 to DNP
    Rise time was slow, causing chip to run bootloader instead of booting from flash
2023-09-21 Docs Update
    Adding smart watch example section along with other minor tweaks to current sections to add necessary info on the example.
2023-09-27 Image dump
    Adding assets folders and contents and adding board images to hardware overview.
2023-10-04 Add Smart Watch Example
2023-10-06 Docs Update
    Adding product photos & updates to docs content w/smart watch demo & other tweaks.
2023-10-10 Update README.md
    Updating readme with product info, photo & related links.
2023-10-10 Update README.md
    Typo fix
2023-10-11 Docs Update
    Updating docs with review changes & software updates.
2023-10-11 Smart Watch Example Update
    Fixing link error & adding profile photos.
2023-10-23 Update mkdocs.yml
    Minor typo in path
2023-10-23 Update software_setup.md
    Update recommended alpha release for ESP32 C6.
2023-11-02 Update intdroduction
    Adding embedded video & formatting.
2023-11-08 Fix typo (LED pin IO20 vs IO23)
2023-12-20 Update introduction.md
    Fix image link
2023-12-20 Update mkdocs.yml
    Update mkdocs.yml with fix for build error.
2023-12-20 Deployed 720135e with MkDocs version: 1.5.3
2024-01-31 Update software setup
    Fixing typo & outdated board info.
2024-01-31 Deployed ee25fd3 with MkDocs version: 1.5.3
2024-04-02 Update smart_watch_example.md
    Fixing incorrect library links to BMA400.
2024-04-02 Update introduction
    Updating smart watch assembly materials with BMA400.
2024-04-02 Deployed b83d06c with MkDocs version: 1.5.3
2024-07-09 Boards Package Update
    Updating software install section for espressif Arduino Boards v3 release including Qwiic Pocket & C6 Thing Plus.
2024-07-09 Deployed e54ac33 with MkDocs version: 1.6.0
2024-10-25 Update mkdocs.yml
    Analytics update.
2024-10-25 Deployed 242b974 with MkDocs version: 1.6.1
